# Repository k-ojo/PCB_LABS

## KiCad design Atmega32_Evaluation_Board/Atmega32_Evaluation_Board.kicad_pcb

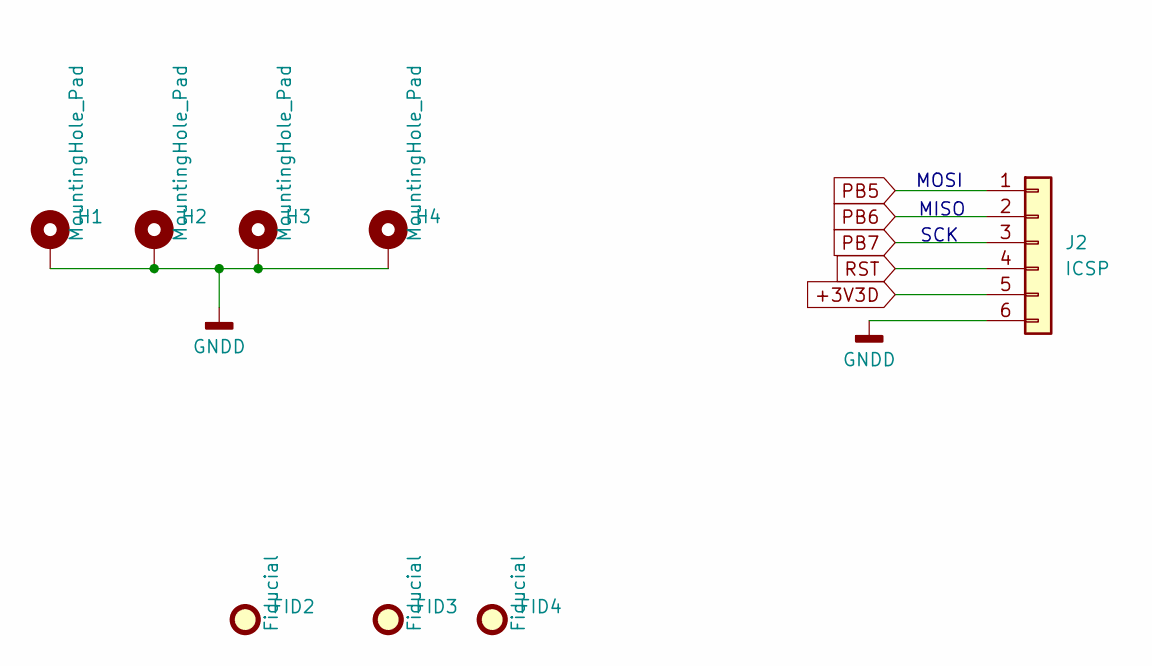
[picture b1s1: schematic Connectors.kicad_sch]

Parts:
FID2, FID3, FID4: Fiducial; Fiducial_0.75mm_Mask2.25mm
H1, H2, H3, H4: MountingHole_Pad; MountingHole_2.5mm_Pad
J2: ICSP; PinHeader_2x03_P2.54mm_Vertical

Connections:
+3V3D: J2.5; also elsewhere on the board
GNDD: H1.1, H2.1, H3.1, H4.1, J2.6; also elsewhere on the board
PB5: J2.1; also elsewhere on the board
PB6: J2.2; also elsewhere on the board
PB7: J2.3; also elsewhere on the board
RST: J2.4; also elsewhere on the board

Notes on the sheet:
SCK
MISO
MOSI

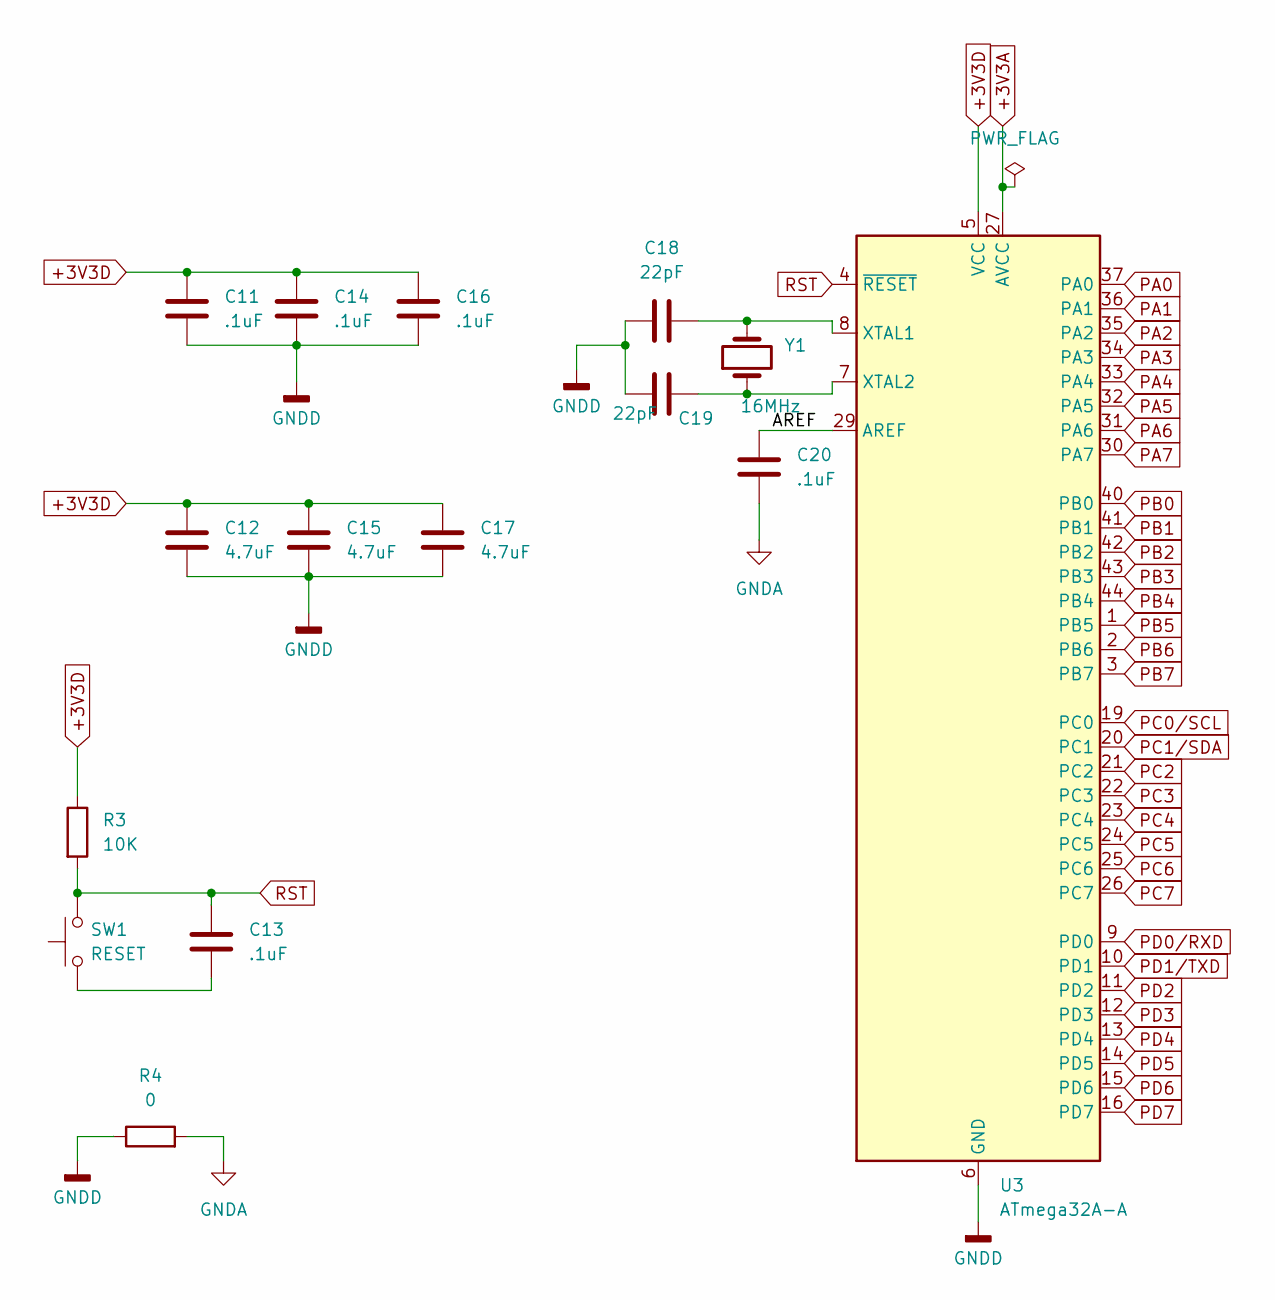
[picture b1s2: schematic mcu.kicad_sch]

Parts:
C11, C13, C14, C16, C20: .1uF; C_0603_1608Metric
C12, C15, C17: 4.7uF; C_0603_1608Metric
C18, C19: 22pF; C_0603_1608Metric
R3: 10K; R_0603_1608Metric
R4: 0; R_0603_1608Metric
SW1: RESET; SW_Push_1P1T-SH_NO_CK_KMR2xxG
U3: ATmega32A-A; TQFP-44_10x10mm_P0.8mm
Y1: 16MHz; Crystal_HC49-4H_Vertical

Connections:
+3V3A: U3.27 (AVCC); also elsewhere on the board
+3V3D: C11.1, C12.1, C14.1, C15.1, C16.1, C17.1, R3.1, U3.5 (VCC), U3.17 (VCC), U3.38 (VCC); also elsewhere on the board
/Microcontroller/AREF: C20.1, U3.29 (AREF)
GNDA: C20.2, R4.2; also elsewhere on the board
GNDD: C11.2, C12.2, C14.2, C15.2, C16.2, C17.2, C18.1, C19.1, R4.1, U3.6 (GND), U3.18 (GND), U3.28 (GND), U3.39 (GND); also elsewhere on the board
unnamed: C13.2, SW1.1
unnamed: C18.2, U3.8 (XTAL1), Y1.2
unnamed: C19.2, U3.7 (XTAL2), Y1.1
PA0: U3.37 (PA0)
PA1: U3.36 (PA1)
PA2: U3.35 (PA2)
PA3: U3.34 (PA3)
PA4: U3.33 (PA4)
PA5: U3.32 (PA5)
PA6: U3.31 (PA6)
PA7: U3.30 (PA7)
PB0: U3.40 (PB0)
PB1: U3.41 (PB1)
PB2: U3.42 (PB2)
PB3: U3.43 (PB3)
PB4: U3.44 (PB4)
PB5: U3.1 (PB5); also elsewhere on the board
PB6: U3.2 (PB6); also elsewhere on the board
PB7: U3.3 (PB7); also elsewhere on the board
PC0/SCL: U3.19 (PC0)
PC1/SDA: U3.20 (PC1)
PC2: U3.21 (PC2)
PC3: U3.22 (PC3)
PC4: U3.23 (PC4)
PC5: U3.24 (PC5)
PC6: U3.25 (PC6)
PC7: U3.26 (PC7)
PD0/RXD: U3.9 (PD0)
PD1/TXD: U3.10 (PD1)
PD2: U3.11 (PD2)
PD3: U3.12 (PD3)
PD4: U3.13 (PD4)
PD5: U3.14 (PD5)
PD6: U3.15 (PD6)
PD7: U3.16 (PD7)
RST: C13.1, R3.2, SW1.2, U3.4 (~RESET); also elsewhere on the board

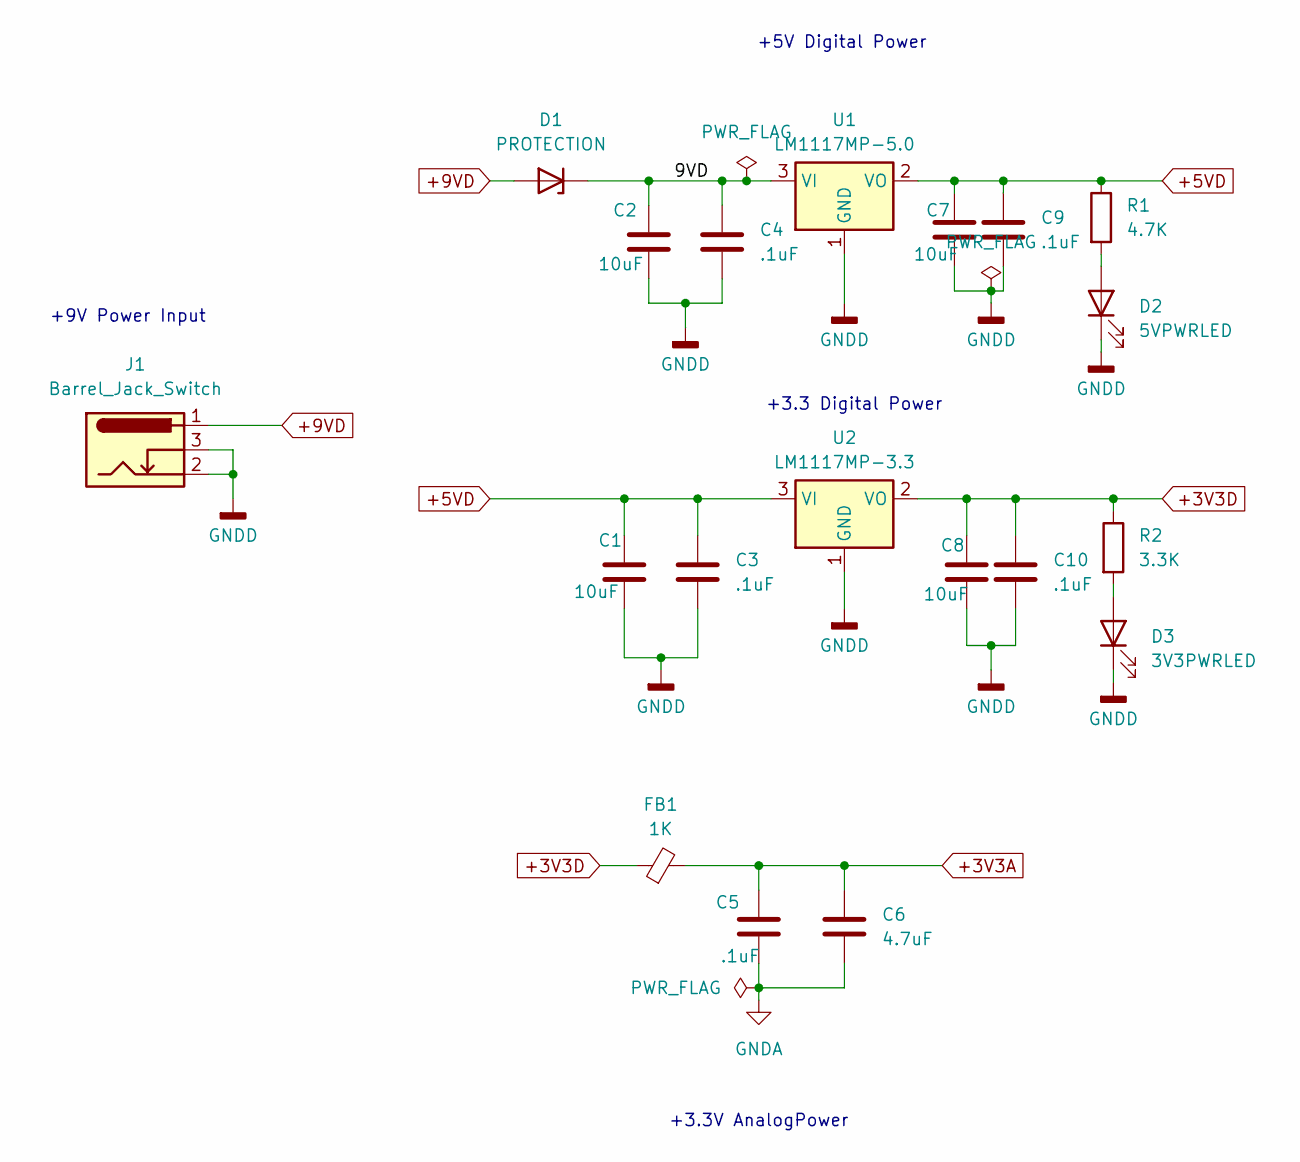
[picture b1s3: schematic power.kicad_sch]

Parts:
C1, C2, C7, C8: 10uF; C_0603_1608Metric
C3, C4, C5, C9, C10: .1uF; C_0603_1608Metric
C6: 4.7uF; C_0603_1608Metric
D1: PROTECTION; D_0603_1608Metric
D2: 5VPWRLED; LED_0603_1608Metric
D3: 3V3PWRLED; LED_0603_1608Metric
FB1: 1K; L_0603_1608Metric
J1: Barrel_Jack_Switch; BarrelJack_Horizontal
R1: 4.7K; R_0603_1608Metric
R2: 3.3K; R_0603_1608Metric
U1: LM1117MP-5.0; SOT-223-3_TabPin2
U2: LM1117MP-3.3; SOT-223-3_TabPin2

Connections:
+3V3A: C5.1, C6.1, FB1.2; also elsewhere on the board
+3V3D: C8.1, C10.1, FB1.1, R2.1, U2.2 (VO); also elsewhere on the board
+5VD: C1.1, C3.1, C7.1, C9.1, R1.1, U1.2 (VO), U2.3 (VI)
+9VD: D1.2 (A), J1.1
/Power/9VD: C2.1, C4.1, D1.1 (K), U1.3 (VI)
GNDA: C5.2, C6.2; also elsewhere on the board
GNDD: C1.2, C2.2, C3.2, C4.2, C7.2, C8.2, C9.2, C10.2, D2.1 (K), D3.1 (K), J1.2, J1.3, U1.1 (GND), U2.1 (GND); also elsewhere on the board
unnamed: D2.2 (A), R1.2
unnamed: D3.2 (A), R2.2

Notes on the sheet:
+5V Digital Power
+3.3V AnalogPower
+9V Power Input
+3.3 Digital Power

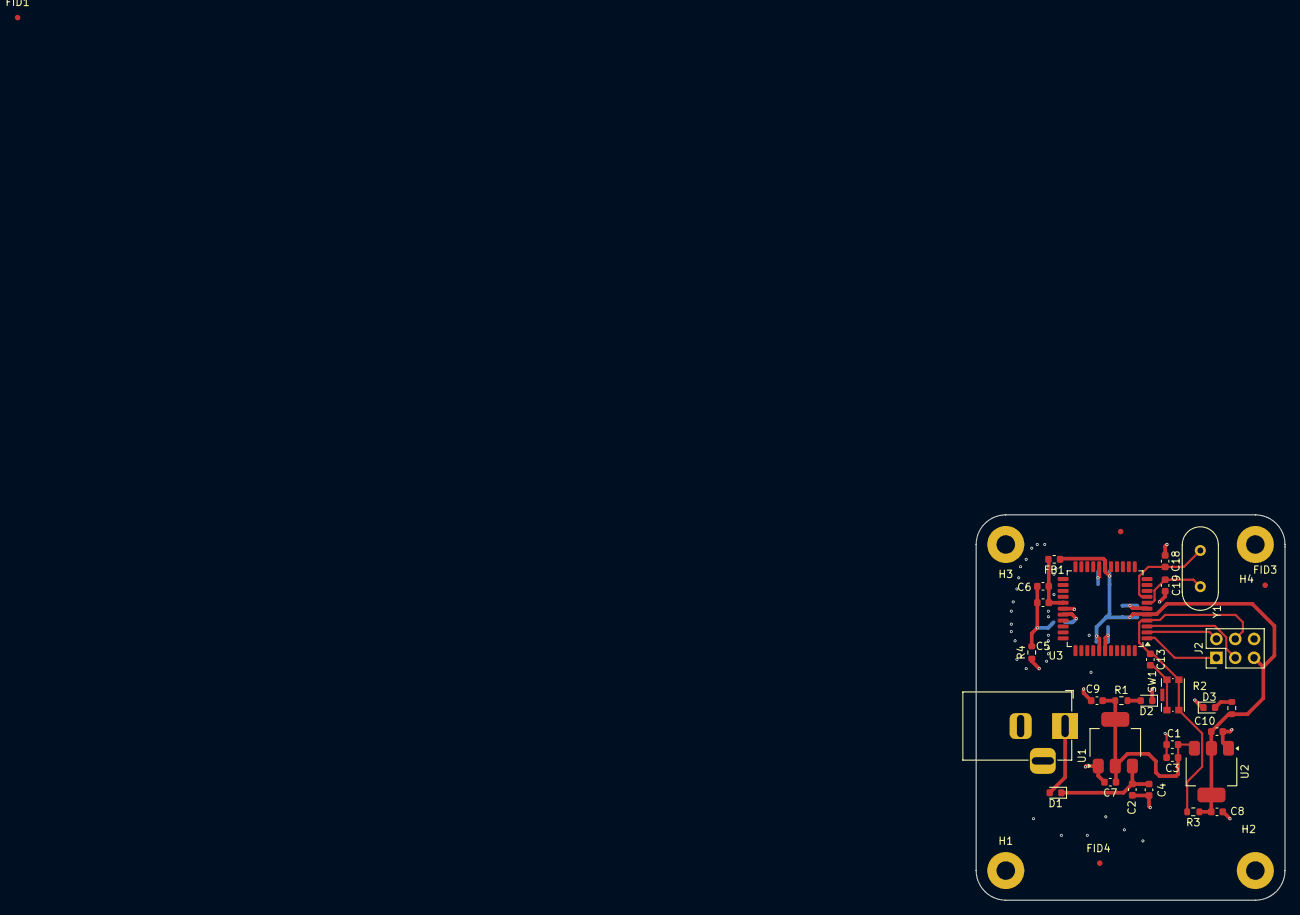
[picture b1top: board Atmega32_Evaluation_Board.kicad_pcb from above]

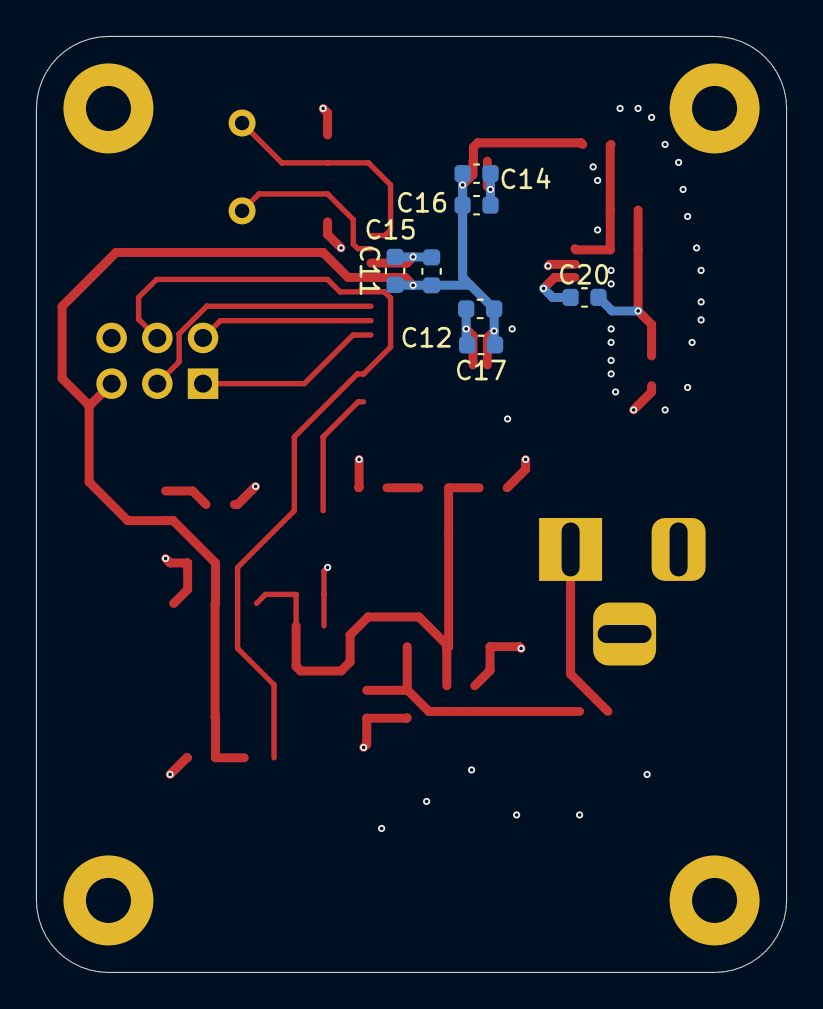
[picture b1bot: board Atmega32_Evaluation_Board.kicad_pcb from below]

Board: 4 copper layers, 41.7 x 52.0 mm, 43 parts (7 on the bottom side), 17 nets.

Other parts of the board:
FID1: Fiducial; Fiducial_0.75mm_Mask2.25mm

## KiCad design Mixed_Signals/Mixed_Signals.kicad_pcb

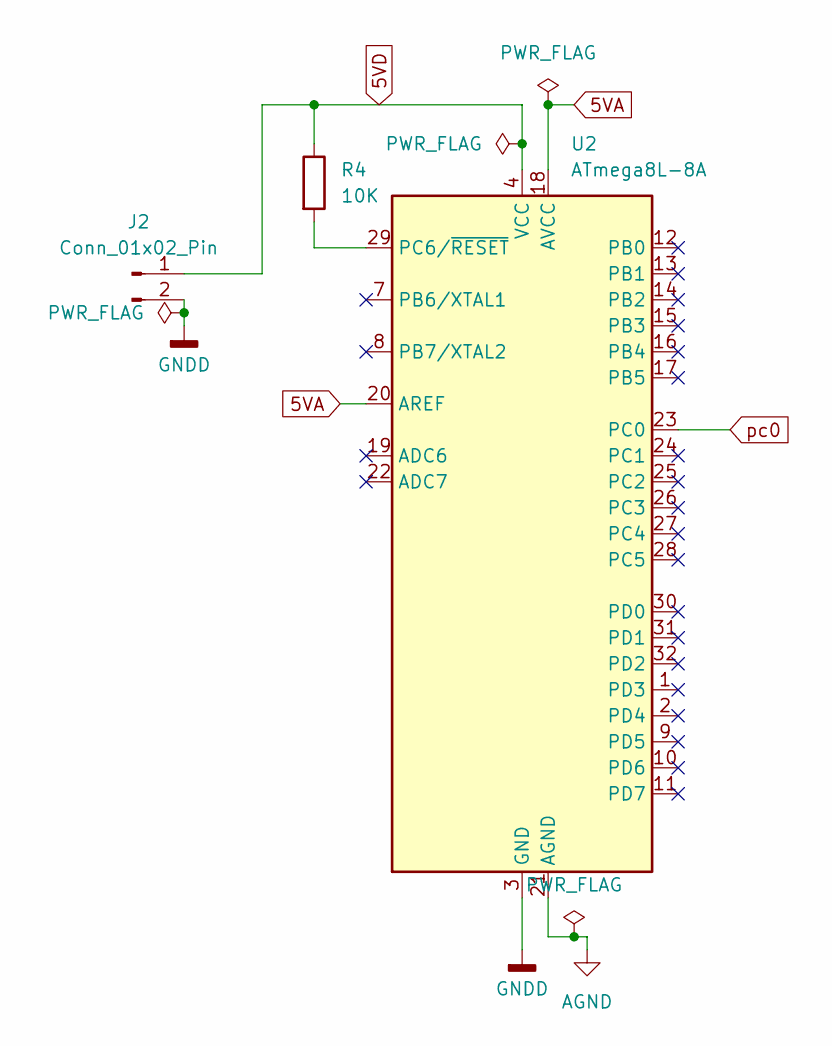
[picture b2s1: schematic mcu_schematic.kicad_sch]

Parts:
J2: Conn_01x02_Pin; PinHeader_1x02_P2.54mm_Vertical
R4: 10K; R_0603_1608Metric
U2: ATmega8L-8A; TQFP-32_7x7mm_P0.8mm

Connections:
5VA: U2.18 (AVCC), U2.20 (AREF); also elsewhere on the board
5VD: J2.1, R4.1, U2.4 (VCC), U2.6 (VCC); also elsewhere on the board
AGND: U2.21 (AGND); also elsewhere on the board
GNDD: J2.2, U2.3 (GND), U2.5 (GND); also elsewhere on the board
unnamed: R4.2, U2.29 (PC6/~RESET)
pc0: U2.23 (PC0); also elsewhere on the board

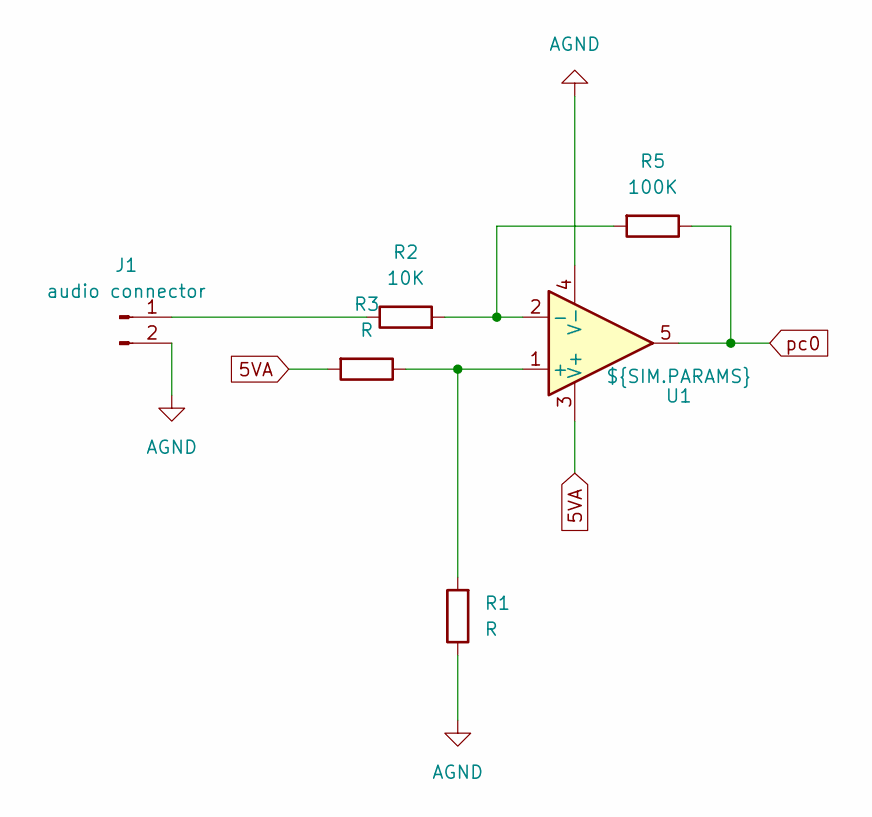
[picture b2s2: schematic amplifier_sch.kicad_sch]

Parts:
J1: audio connector; PinHeader_1x02_P2.54mm_Vertical
R1, R3: R; R_0603_1608Metric
R2: 10K; R_0603_1608Metric
R5: 100K; R_0603_1608Metric
U1: ${SIM.PARAMS}; SOIC-8_3.9x4.9mm_P1.27mm

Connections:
5VA: R3.2, U1.3 (V+); also elsewhere on the board
AGND: J1.2, R1.1, U1.4 (V-); also elsewhere on the board
unnamed: J1.1, R2.1
unnamed: R1.2, R3.1, U1.1 (+)
unnamed: R2.2, R5.2, U1.2 (-)
pc0: R5.1, U1.5; also elsewhere on the board

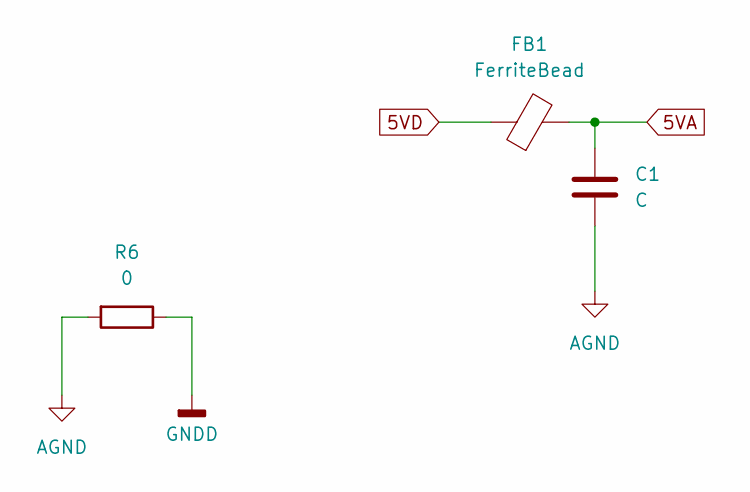
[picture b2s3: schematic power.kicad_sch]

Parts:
C1: C; C_0603_1608Metric
FB1: FerriteBead; L_0603_1608Metric
R6: 0; R_0603_1608Metric

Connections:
5VA: C1.1, FB1.2; also elsewhere on the board
5VD: FB1.1; also elsewhere on the board
AGND: C1.2, R6.2; also elsewhere on the board
GNDD: R6.1; also elsewhere on the board

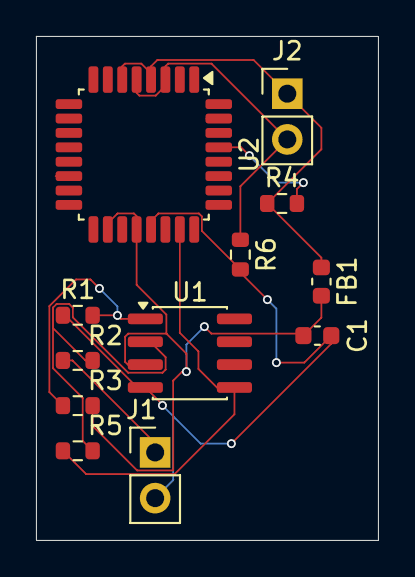
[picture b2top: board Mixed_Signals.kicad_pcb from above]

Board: 2 copper layers, 19.0 x 28.0 mm, 12 parts (0 on the bottom side), 9 nets.

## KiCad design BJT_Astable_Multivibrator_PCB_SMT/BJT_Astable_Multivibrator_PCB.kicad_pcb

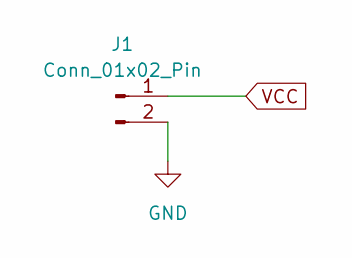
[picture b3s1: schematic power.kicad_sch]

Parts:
J1: Conn_01x02_Pin; PinHeader_1x02_P2.00mm_Vertical

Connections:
GND: J1.2; also elsewhere on the board
VCC: J1.1; also elsewhere on the board

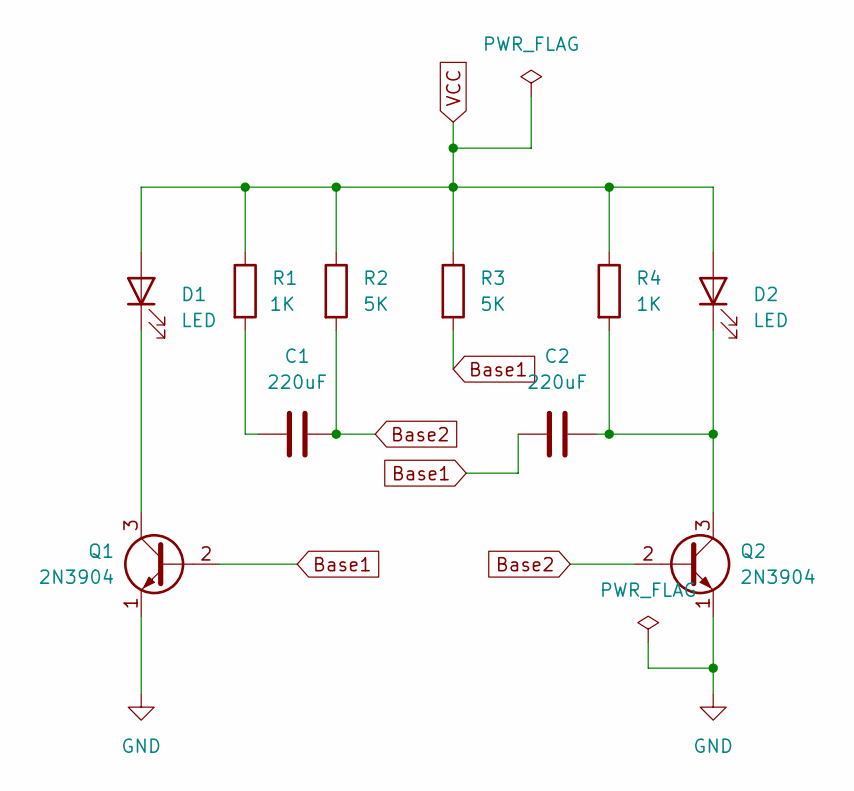
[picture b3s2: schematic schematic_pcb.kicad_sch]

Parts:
C1, C2: 220uF; C_0603_1608Metric
D1, D2: LED; LED_0603_1608Metric
Q1, Q2: 2N3904; SOT-23
R1, R4: 1K; R_0603_1608Metric
R2, R3: 5K; R_0603_1608Metric

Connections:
Base1: C2.2, Q1.2 (B), R3.2
Base2: C1.1, Q2.2 (B), R2.2
GND: Q1.1 (E), Q2.1 (E); also elsewhere on the board
unnamed: C1.2, R1.2
unnamed: D1.1 (K), Q1.3 (C)
unnamed: C2.1, D2.1 (K), Q2.3 (C), R4.2
VCC: D1.2 (A), D2.2 (A), R1.1, R2.1, R3.1, R4.1; also elsewhere on the board

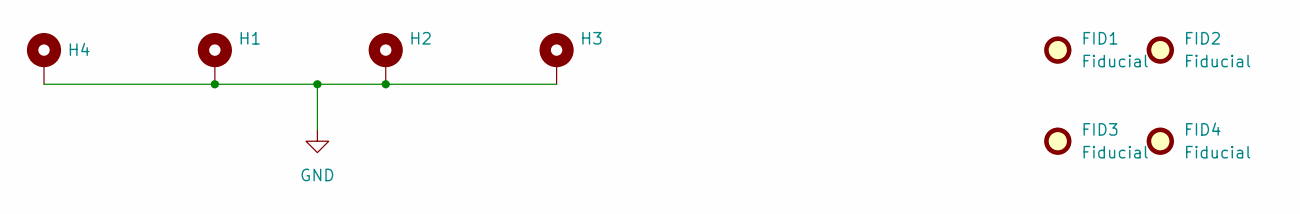
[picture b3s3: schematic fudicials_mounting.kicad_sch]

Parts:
FID1, FID2, FID3, FID4: Fiducial; Fiducial_0.75mm_Mask1.5mm
H1, H2, H3, H4: MountingHole_Pad; MountingHole_2.5mm_Pad

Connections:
GND: H1.1, H2.1, H3.1, H4.1; also elsewhere on the board

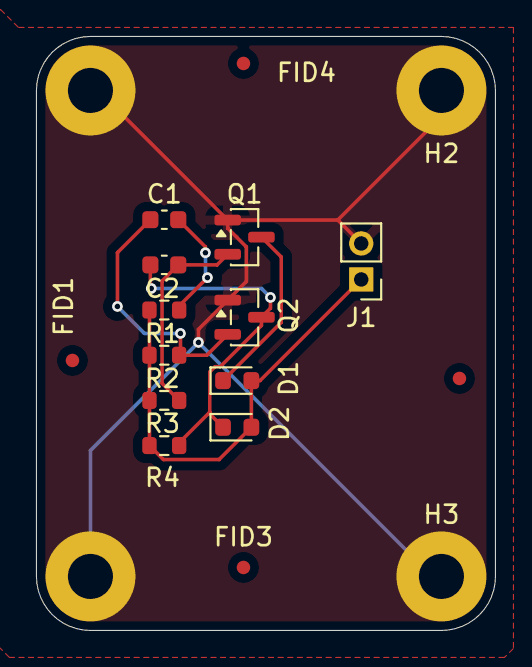
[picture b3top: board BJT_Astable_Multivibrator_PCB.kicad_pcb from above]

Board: 2 copper layers, 25.5 x 33.0 mm, 19 parts (0 on the bottom side), 7 nets.

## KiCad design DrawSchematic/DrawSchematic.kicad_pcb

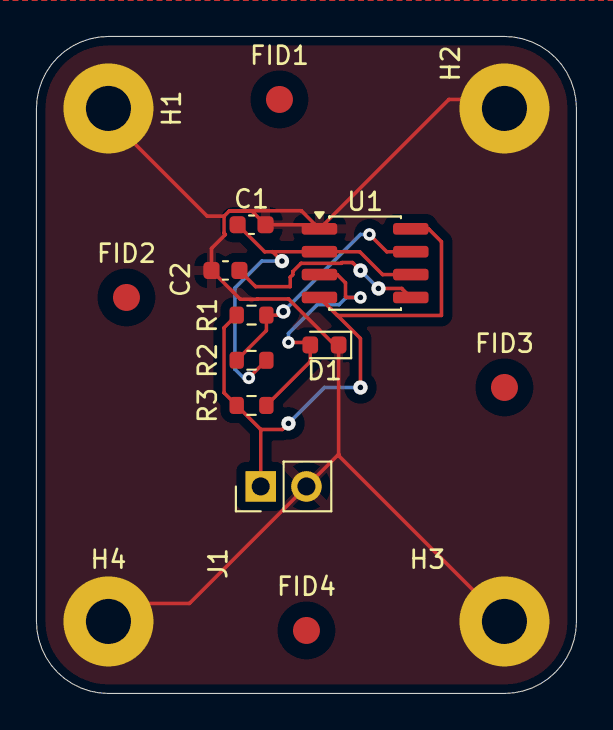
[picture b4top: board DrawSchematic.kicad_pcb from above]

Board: 2 copper layers, 30.0 x 36.5 mm, 16 parts (0 on the bottom side), 6 nets.

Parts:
C1: 0.1uF; C_0603_1608Metric
C2: 0.01uF; C_0603_1608Metric
D1: LED; LED_0603_1608Metric
FID1, FID2, FID3, FID4: Fiducial; Fiducial_1.5mm_Mask3mm
H1, H2, H3, H4: MountingHole_Pad; MountingHole_2.5mm_Pad
J1: POWER INPUT; PinHeader_1x02_P2.54mm_Vertical
R1, R2: 10K; R_0603_1608Metric
R3: 1K; R_0603_1608Metric
U1: LM555xN; SOP-8_3.76x4.96mm_P1.27mm

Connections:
DIS: R1.2, R2.1, U1.7 (DIS)
GND: C1.2, C2.2, D1.1 (K), H1.1, H2.1, H3.1, H4.1, J1.2, U1.1 (GND)
unnamed: D1.2 (A), R3.2, U1.3 (Q)
unnamed: C2.1, U1.5 (CV)
TRG: C1.1, R2.2, U1.2 (TR), U1.6 (THR)
VCC: J1.1, R1.1, R3.1, U1.4 (R), U1.8 (VCC)

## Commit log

2025-10-31 added first project with 555 timer
2025-10-31 added PCB 3D view to readme
2025-10-31 Center align 3D PCB image in README
    Updated image formatting for 3D PCB view.
2025-11-01 added BJT Astable Multivibrator
2025-11-11 added smt design of BJT mulitvibrator
2025-11-13 added logo library
2025-11-13 Renamed amplifier schematic
2025-11-13 cleaned up
2025-11-14 modified board
2025-11-14 added screenshots
2025-11-14 added
2025-11-14 added README.md
2025-11-14 Fix logo image path in README.md
2025-11-14 Rename Pilolo Electronics.png to logo.png
2025-11-14 Fix image tags in README.md
    Updated README to include proper image tags for logo and PCB views.
2025-11-14 added logo to readme
2025-11-14 modified amplifier_sch
2025-11-14 Fixed voltage divider error
2025-11-14 modified schematics
2025-11-23 added msp project
2025-11-24 added Atmega project
2025-11-24 updated main readme
